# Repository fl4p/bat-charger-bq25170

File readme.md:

Tiny battery charger featuring BQ25170.
Output voltage and current programmable through resistors.

|      |           |
|------|-----------|
| Vin  | 3..6V     |
| Vout | 3.5..4.4V |
| Iout | 10..800mA |

* LiFePO4: 3.5 V, 3.6 V, 3.7 V
* Li-Ion:  4.05 V, 4.1 V, 4.2 V, 4.35 V, 4.4 V
* Na-ion (Sodium)

```
R1 (Vset)
3.6V	82k
3.7V	62k
4.1V	36k
4.2V	27k
```

```
R2 (Iset)
800mA	375Ω
500mA	600Ω
```

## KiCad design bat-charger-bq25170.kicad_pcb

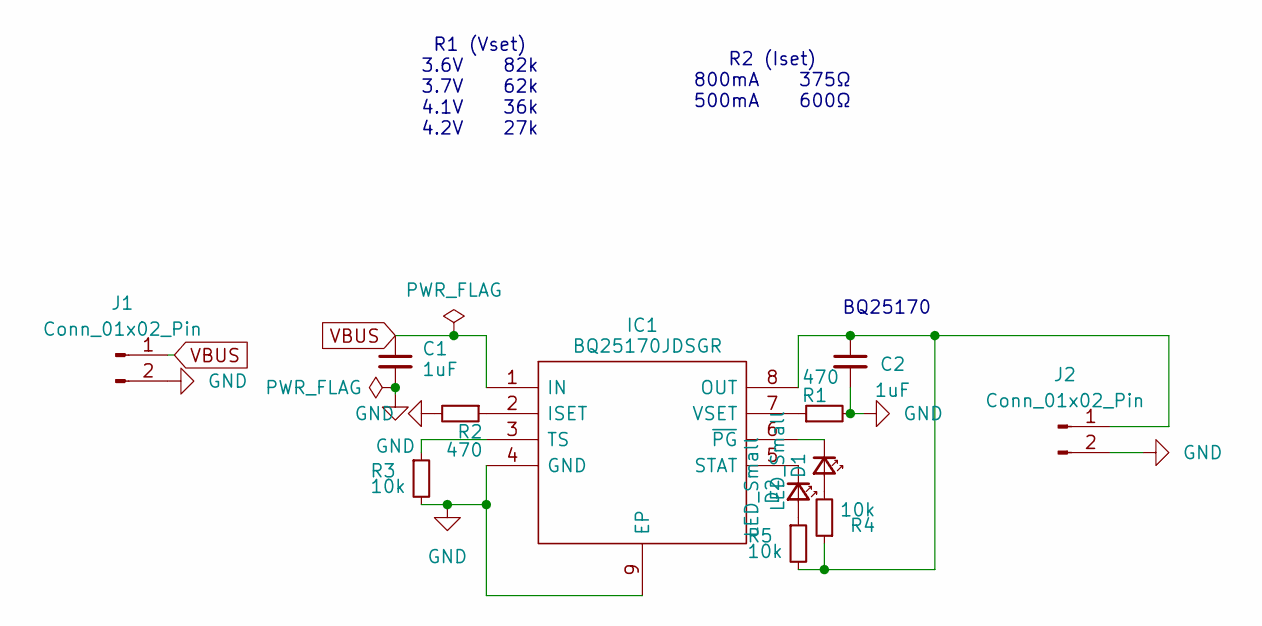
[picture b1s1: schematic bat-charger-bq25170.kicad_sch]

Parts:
C1, C2: 1uF; C_0603_1608Metric_Pad1.08x0.95mm_HandSolder
D1, D2: LED_Small; LED_0603_1608Metric
IC1: BQ25170JDSGR; WSON-8-1EP_2x2mm_P0.5mm_EP0.9x1.6mm; Mouser Part Number 595-BQ25170JDSGR
J1, J2: Conn_01x02_Pin; PinHeader_1x02_P2.54mm_Vertical
R1, R2: 470; R_0603_1608Metric
R3, R4, R5: 10k; C_0603_1608Metric

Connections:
GND: C1.2, C2.2, IC1.4 (GND), IC1.9 (EP), J1.2, J2.2, R1.2, R2.2, R3.2
unnamed: D1.2 (A), R4.2
unnamed: D1.1 (K), IC1.6 (~PG)
unnamed: D2.2 (A), R5.1
unnamed: D2.1 (K), IC1.5 (STAT)
unnamed: IC1.2 (ISET), R2.1
unnamed: C2.1, IC1.8 (OUT), J2.1, R4.1, R5.2
unnamed: IC1.3 (TS), R3.1
unnamed: IC1.7 (VSET), R1.1
VBUS: C1.1, IC1.1 (IN), J1.1

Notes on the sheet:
BQ25170
R2 (Iset) 800mA 375Ω 500mA 600Ω
R1 (Vset) 3.6V 82k 3.7V 62k 4.1V 36k 4.2V 27k

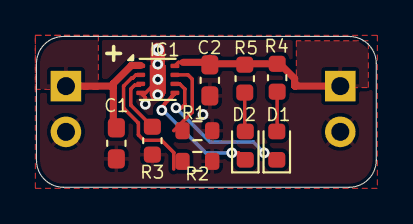
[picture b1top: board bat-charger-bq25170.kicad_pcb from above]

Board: 2 copper layers, 18.9 x 8.4 mm, 12 parts (0 on the bottom side), 10 nets.

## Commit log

2025-11-07 init
2025-11-07 fix img
